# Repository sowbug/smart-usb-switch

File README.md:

# smart-usb-switch

An inline USB type-A power switch that's controlled by an ESP8266 (ESP-12F) on
GPIO4. You can load this device with any firmware you want, including for
example [ESPHome](https://esphome.io).

Version 2 has two buttons on the back. If you build this board yourself, you can
put 0, 1, or 2 of the button components in place.

The PCB could probably be a little smaller, but the ESP-12F takes up a lot of
real estate.

## How to program

These instructions are for ESPHome, but since it's just an ESP8266, you can do
anything you want instead.

Soldering jumper pins on the terminal points is optional. Get ESPHome ready with
a .yaml file like the one included in this project. Connect the PROG terminals
to each other. Using a USB-TTL adapter _that is configured to use 3.3-volt logic
levels_, connect GND, 3V3, TX, RX (in other words, match up the labels on the
USB-TTL adapter with the ones on the smart switch, but connect RX to TXD and TX
to RXD). Then build the ESPHome image and upload with
`esphome your-config.yaml run` or however else you use ESPHome.

## Bill of Materials

See `smart-usb-switch.csv`.

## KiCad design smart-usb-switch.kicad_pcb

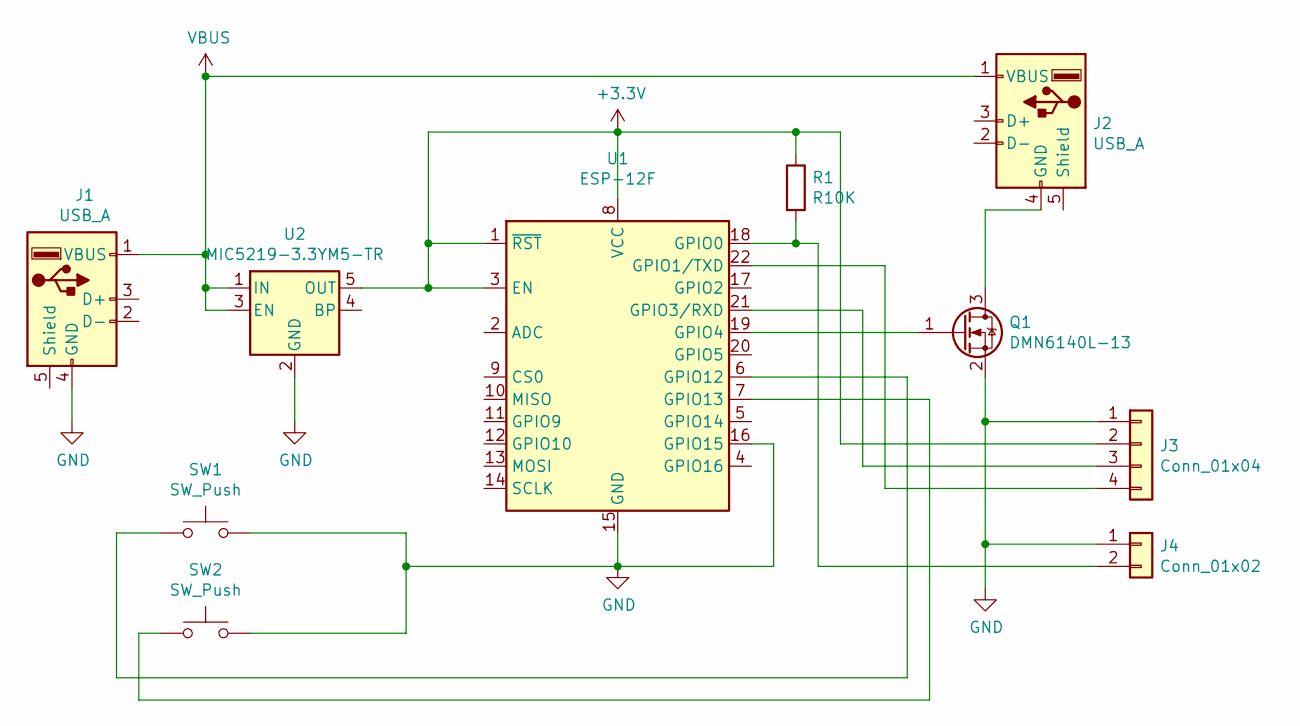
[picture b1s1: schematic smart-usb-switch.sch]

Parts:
J1: USB_A; USB_A_CNCTech_1001-011-01101_Horizontal; LCSC C46394
J2: USB_A; USB_A_Stewart_SS-52100-001_Horizontal; LCSC C86461
J3: Conn_01x04; PinHeader_1x04_P2.54mm_Vertical
J4: Conn_01x02; PinHeader_1x02_P2.54mm_Vertical
Q1: DMN6140L-13; SOT-23; LCSC C211403
R1: R10K; R_0805_2012Metric; LCSC C17414
SW1, SW2: SW_Push; SW_SPST_SKQG_WithStem; LCSC C318888
U1: ESP-12F; ESP-12E; LCSC C82891
U2: MIC5219-3.3YM5-TR; SOT-23-5; LCSC C29613

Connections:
+3V3: J3.2, R1.1, U1.1 (~RST), U1.3 (EN), U1.8 (VCC), U2.5 (OUT)
GND: J1.4 (GND), J3.1, J4.1, Q1.2 (S), SW1.2, SW2.2, U1.15 (GND), U1.16 (GPIO15), U2.2 (GND)
unnamed: J2.4 (GND), Q1.3 (D)
unnamed: J3.3, U1.21 (GPIO3/RXD)
unnamed: J3.4, U1.22 (GPIO1/TXD)
unnamed: J4.2, R1.2, U1.18 (GPIO0)
unnamed: Q1.1 (G), U1.19 (GPIO4)
unnamed: SW1.1, U1.6 (GPIO12)
unnamed: SW2.1, U1.7 (GPIO13)
VBUS: J1.1 (VBUS), J2.1 (VBUS), U2.1 (IN), U2.3 (EN)

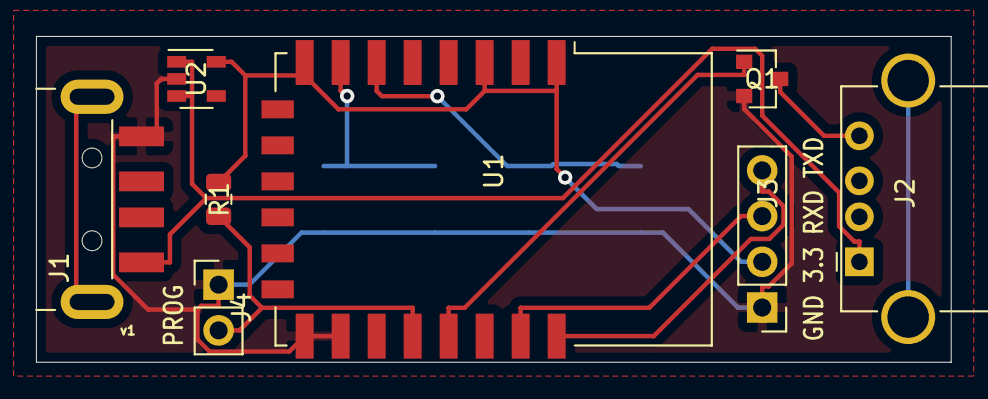
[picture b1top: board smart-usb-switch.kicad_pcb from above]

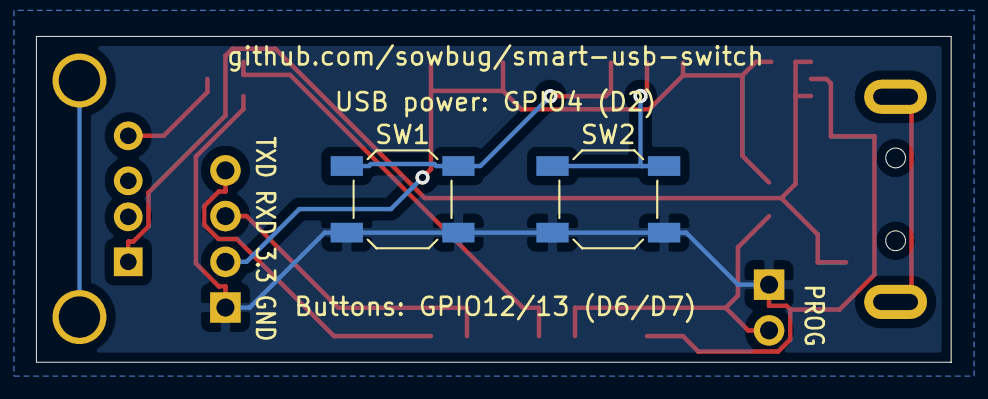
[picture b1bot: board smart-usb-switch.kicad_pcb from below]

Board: 2 copper layers, 50.8 x 18.1 mm, 10 parts (2 on the bottom side), 10 nets.

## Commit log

2019-12-10 First commit after successful build.
    Built at https://oshpark.com/shared_projects/oemoKIwf
    Main bug with this version is the switch flashes briefly on
    when it's first plugged in.
2019-12-10 README
2019-12-10 Fix #1: switch to GPIO4
2019-12-10 Updated current components
2019-12-10 more docs, updates
2019-12-10 Fix #2: change to non-heavy duty Molex USB plug
2019-12-10 Update bug status
2019-12-10 Socket datasheets
2019-12-10 Molex 480371000
2019-12-11 reroute
2019-12-11 update schematic image
2019-12-11 GPIO14 -> GPIO4
2020-01-08 update components to standard library
2020-01-09 Add buttons. Reroute, improve docs
2020-01-25 Make board narrower so it's more likely to fit in side-by-side USB ports
2020-01-27 Update artifacts and samples
2020-02-02 re-route with freerouting.org
2020-02-15 Add machine-readable BOM and LCSC part numbers
2020-02-15 more things to ignore
2020-02-15 More LCSC and docs
2020-02-15 JLCPCB mfg
2020-02-15 Update BOM reference
2020-09-18 Update to v2 output GPIO
